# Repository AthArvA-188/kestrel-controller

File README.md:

# Kestrel

Kestrel is a design for a game controller that works with PC, Android, iPhone, and iPad. This repository holds the electronics, the enclosure, and the firmware.

Status: design files only. Nobody has built or tested a Kestrel. Every part of the design needs a prototype before it can be trusted.

## What the design covers

| Requirement | How the design answers it |
| --- | --- |
| USB-C, Bluetooth, WiFi | ESP32-S3 module with native USB, Bluetooth LE, and WiFi |
| Remote play over WiFi | The pad sends inputs straight to a receiver on the gaming PC |
| Xbox layout | Offset sticks, ABXY, D-pad, View, Menu, Home, bumpers, triggers |
| TMR sticks with a tension ring | TMR modules in the ALPS footprint. A ring under each stick preloads an added centring spring |
| Adaptive triggers | A motor, worm, and stop arm per trigger, with Hall position sensing |
| Tactile LB and RB | Micro switches |
| Four back paddles | Two per grip on micro switches, remappable |
| Backlit controls | 24 addressable RGB LEDs under translucent buttons and stick rings |
| Screen | 1.9 inch 320 x 170 display showing host, battery, and profile, with on-device remapping |
| XInput and DInput | Both over USB. Bluetooth offers an Xbox identity and a generic gamepad |
| Wider grip | 173 mm wide body with full grips |

`docs/spec.md` explains each decision.

## Layout

| Folder | Contents | Start with |
| --- | --- | --- |
| `docs/` | Specification and WiFi protocol | `docs/spec.md` |
| `shared/` | Coordinates and pin assignments that the other folders read | `layout.json`, `pinmap.json` |
| `hardware/` | KiCad schematic and PCB, generator scripts, fabrication files | `hardware/README.md` |
| `mech/` | Enclosure and mechanism CAD, STEP and STL files, renders | `mech/README.md` |
| `firmware/` | ESP-IDF firmware, native tests, screen simulator | `firmware/README.md` |
| `host/` | PC receiver for WiFi mode | `host/README.md` |

## What has been checked

| Area | Checked | Not checked |
| --- | --- | --- |
| Schematic | KiCad electrical rules check | Review by a second engineer |
| PCB | KiCad design rules check and schematic parity. Results are in `hardware/README.md` | Fabrication, assembly, power-up |
| Enclosure | Part interference, stick tilt clearance, trigger sweep, opening positions | Printing, fit, strength, feel |
| Firmware | Builds for the ESP32-S3. 49 unit tests pass on a PC. The screen UI renders in a simulator | Anything on hardware |
| WiFi receiver | 23 tests pass against a simulated pad | The virtual gamepad driver |

The screen UI below comes from the real firmware code running in the simulator.

## Biggest risks

1. **iPhone and iPad.** iOS only accepts known controllers. The firmware presents an Xbox controller's Bluetooth identity, and nobody has confirmed that this works from an ESP32. Treat Apple support as unproven.
2. **The PCB is autorouted.** It passes the rule checks, but the router ran signal tracks through the inner power layers. A layout engineer should review it before a production order. See `hardware/README.md`.
3. **The stick tension mechanism is new.** Its forces are calculated, not measured, and it may make L3 and R3 click too easily on the tightest setting.
4. **The trigger actuator is first-pass.** The gear ratio, motor, and arm geometry need tuning on a prototype.
5. **Parts need checking against their drawings.** The thumbstick module's supply pins, the micro switch footprint, the fuel gauge footprint, and the display module's pocket are listed in `docs/spec.md` under open items.

## Building a prototype

1. Read the open items in `docs/spec.md` and the "Before ordering" list in `hardware/README.md`.
2. Order the PCB from `hardware/out/fab/` and the parts in `hardware/out/kestrel-bom.csv`.
3. Print the parts in `mech/out/stl/`.
4. Build and flash the firmware as `firmware/README.md` describes.
5. Run stick, trigger, and bumper calibration from the on-screen menu.

## Third-party material

- The schematic and PCB embed symbols and footprints from the KiCad libraries, which use the CC-BY-SA 4.0 licence with an exception for designs.
- `hardware/lib/easyeda/` holds the thumbstick symbol, footprint, and 3D model converted from the EasyEDA library entry for LCSC part C146170. Check EasyEDA's terms before publishing them.
- The firmware font is generated from Aileron, a CC0 typeface.
- The Xbox-identity Bluetooth mode uses Microsoft's vendor ID and report format. That suits a personal prototype and is not cleared for a product on sale. The USB vendor ID `1209:0001` is a placeholder.

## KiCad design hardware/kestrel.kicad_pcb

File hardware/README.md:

# Kestrel main board

One four-layer PCB, 134 x 82 mm, carrying everything except the display module, battery, motors, and paddle switches. Scripts generate the schematic, the board, and the fabrication files from `gen/design.py`.

Status: generated and rule-checked. Nobody has fabricated or powered this board. Read "Before ordering" below.

## Files

| Path | Contents |
| --- | --- |
| `kestrel.kicad_pro`, `kestrel.kicad_sch`, `kestrel.kicad_pcb` | KiCad 10 project |
| `gen/` | Generator scripts. `design.py` holds the parts, nets, and placement |
| `lib/` | Project libraries: the fuel gauge symbol, the micro switch footprint, and the thumbstick part from EasyEDA |
| `out/kestrel-schematic.pdf` | Schematic |
| `out/kestrel-bom.csv` | Bill of materials, 47 lines |
| `out/fab/` | Gerbers, drill files, and the position file |
| `out/kestrel-pcb.step` | 3D model of the assembled board |
| `out/erc.json`, `out/drc.json` | Rule check reports |

## Checks

Results from the last run:

| Check | Result |
| --- | --- |
| Electrical rules check on the schematic | 0 violations. 190 symbols, 130 nets |
| Design rules check on the board | 0 errors, 102 warnings. Every warning is silkscreen text over copper, over other text, or near the edge |
| Unconnected items | 0 |
| Schematic parity (board nets and footprints against the schematic) | 0 differences |

The board has 193 footprints, 2481 track segments totalling 6.2 m, and 353 vias.

The rule set: 0.2 mm tracks and 0.15 mm clearance by default, 0.4 mm for power nets, 0.6 mm vias with 0.3 mm holes, 0.3 mm copper-to-edge. The autorouter narrows a few tracks to 0.1 mm at fine-pitch pins, so the minimum track width is 0.1 mm. These fit a standard four-layer service such as JLCPCB's. Confirm against your fabricator's limits.

## Layers

| Layer | Use |
| --- | --- |
| F.Cu | Face-side parts, signals, a VLED pour, and a VSYS pour over the power section |
| In1.Cu | Ground plane, with signal tracks through it |
| In2.Cu | VLED plane, with signal tracks through it |
| B.Cu | Battery-side parts, signals, a ground pour, and a VSYS pour |

VLED is the switched rail that feeds the LEDs and rumble motors. VSYS is the charger's system output.

The autorouter put 3.9 m of the 6.2 m of track on the two inner layers. Those tracks cut both planes into pieces. The finish stage joins the pieces again: each rail has copper on a second layer, and vias tie every island of one layer to the other. The board is fully connected, but neither inner layer is a solid plane. This is the board's main weakness. Before a production order, a layout engineer should move the signals off In1 so the ground plane is unbroken.

## Where things are

Face side: both thumbsticks, twelve tact switches, 24 LEDs with their capacitors, the LB and RB micro switches, the USB-C socket, the display connector, and the power section (charger, buck-boost, fuel gauge, load switches, 3.0 V regulator) under the display.

Battery side: the ESP32-S3 module with its antenna over the rear edge, three shift registers with pull-up arrays, the trigger motor driver, the Hall sensors, the rumble drivers, and the connectors.

| Connector | Type | Pins |
| --- | --- | --- |
| J1 | USB-C | USB 2.0 |
| J2 | JST-PH 2 | 1 battery +, 2 ground |
| J3, J4 | JST-SH 2 | Left and right trigger motors |
| J5, J6 | JST-SH 2 | Left and right rumble motors: 1 VLED, 2 switched return |
| J7, J8 | JST-SH 3 | Paddle switches: two inputs and ground |
| J9 | JST-GH 8 | Display module: VCC, GND, DIN, CLK, CS, DC, RST, BL |
| J10 | 1.27 mm header | 3V3, GND, UART TX, UART RX, EN, BOOT |

JP1 to JP4 are three-pad solder jumpers that set which outer pin of each thumbstick axis gets 3.0 V and which gets ground. They ship bridged for 3.0 V on pads 3 and 4.

SW13 is BOOT and SW14 is RESET. The bottom shell has a pinhole over each.

## Regenerating

The scripts need KiCad 10, Java 21 or later, and the Freerouting jar. Set `KICAD_ROOT` and `FREEROUTING_JAR` if they are not in the default locations at the top of `gen/build.py`. Run with KiCad's own Python:

```powershell
cd hardware\gen
$py = "$env:KICAD_ROOT\bin\python.exe"
& $py build.py sch       # schematic, ERC, PDF, netlist
& $py build.py pcb       # placed board, placement DRC, autorouter input
& $py build.py route     # autoroute (about 25 minutes), then the finish stage
& $py build.py outputs   # Gerbers, drill, position, BOM, STEP, renders
```

`build.py finish` repeats the finish stage on the saved autorouter session: it rebuilds the placed board, imports the routes, adds the pours, joins the copper islands, routes any stranded pad to its rail, and runs DRC.

The autorouter gives a different result on every run. A new run can leave a pin stranded that the finish stage cannot reach. Check that DRC reports 0 unconnected items before using the output.

`build.py route3` is an experiment that keeps In1 as a solid ground plane. It left about 40 signal connections unrouted, so the delivered board does not use it.

## Before ordering

1. **Thumbstick supply pins.** Find which outer pin of each axis is the supply on your TMR module and set JP1 to JP4 before first power-up. A reversed supply may damage the module.
2. **Thumbstick footprint.** It is the ALPS RKJXV1224005 footprint from EasyEDA. Check it against your module.
3. **Micro switch footprint.** `SW_D2FC_THT` is drawn from the usual D2FC dimensions: three pins at 5.08 mm in a 12.8 x 5.8 mm body. Check it against your switch.
4. **Fuel gauge footprint.** The MAX17048 uses KiCad's generic 2 x 2 mm DFN-8. Check the pad sizes against the datasheet.
5. **Display cable.** J9 follows the Waveshare 1.9inch LCD Module's pin order. Check the order on your module and cable.
6. **Layout review.** See "Layers". Also check the 0.4 mm power tracks against your current needs. The USB data pair is not length-matched or impedance-controlled, which full-speed USB tolerates.
7. **Parts.** Nobody has checked the BOM for stock, price, or alternates. Passive voltage ratings are given only where they matter.
8. **Charging.** The input limit is 500 mA. The TS pin has a fixed 10k resistor, so the charger does not monitor battery temperature.

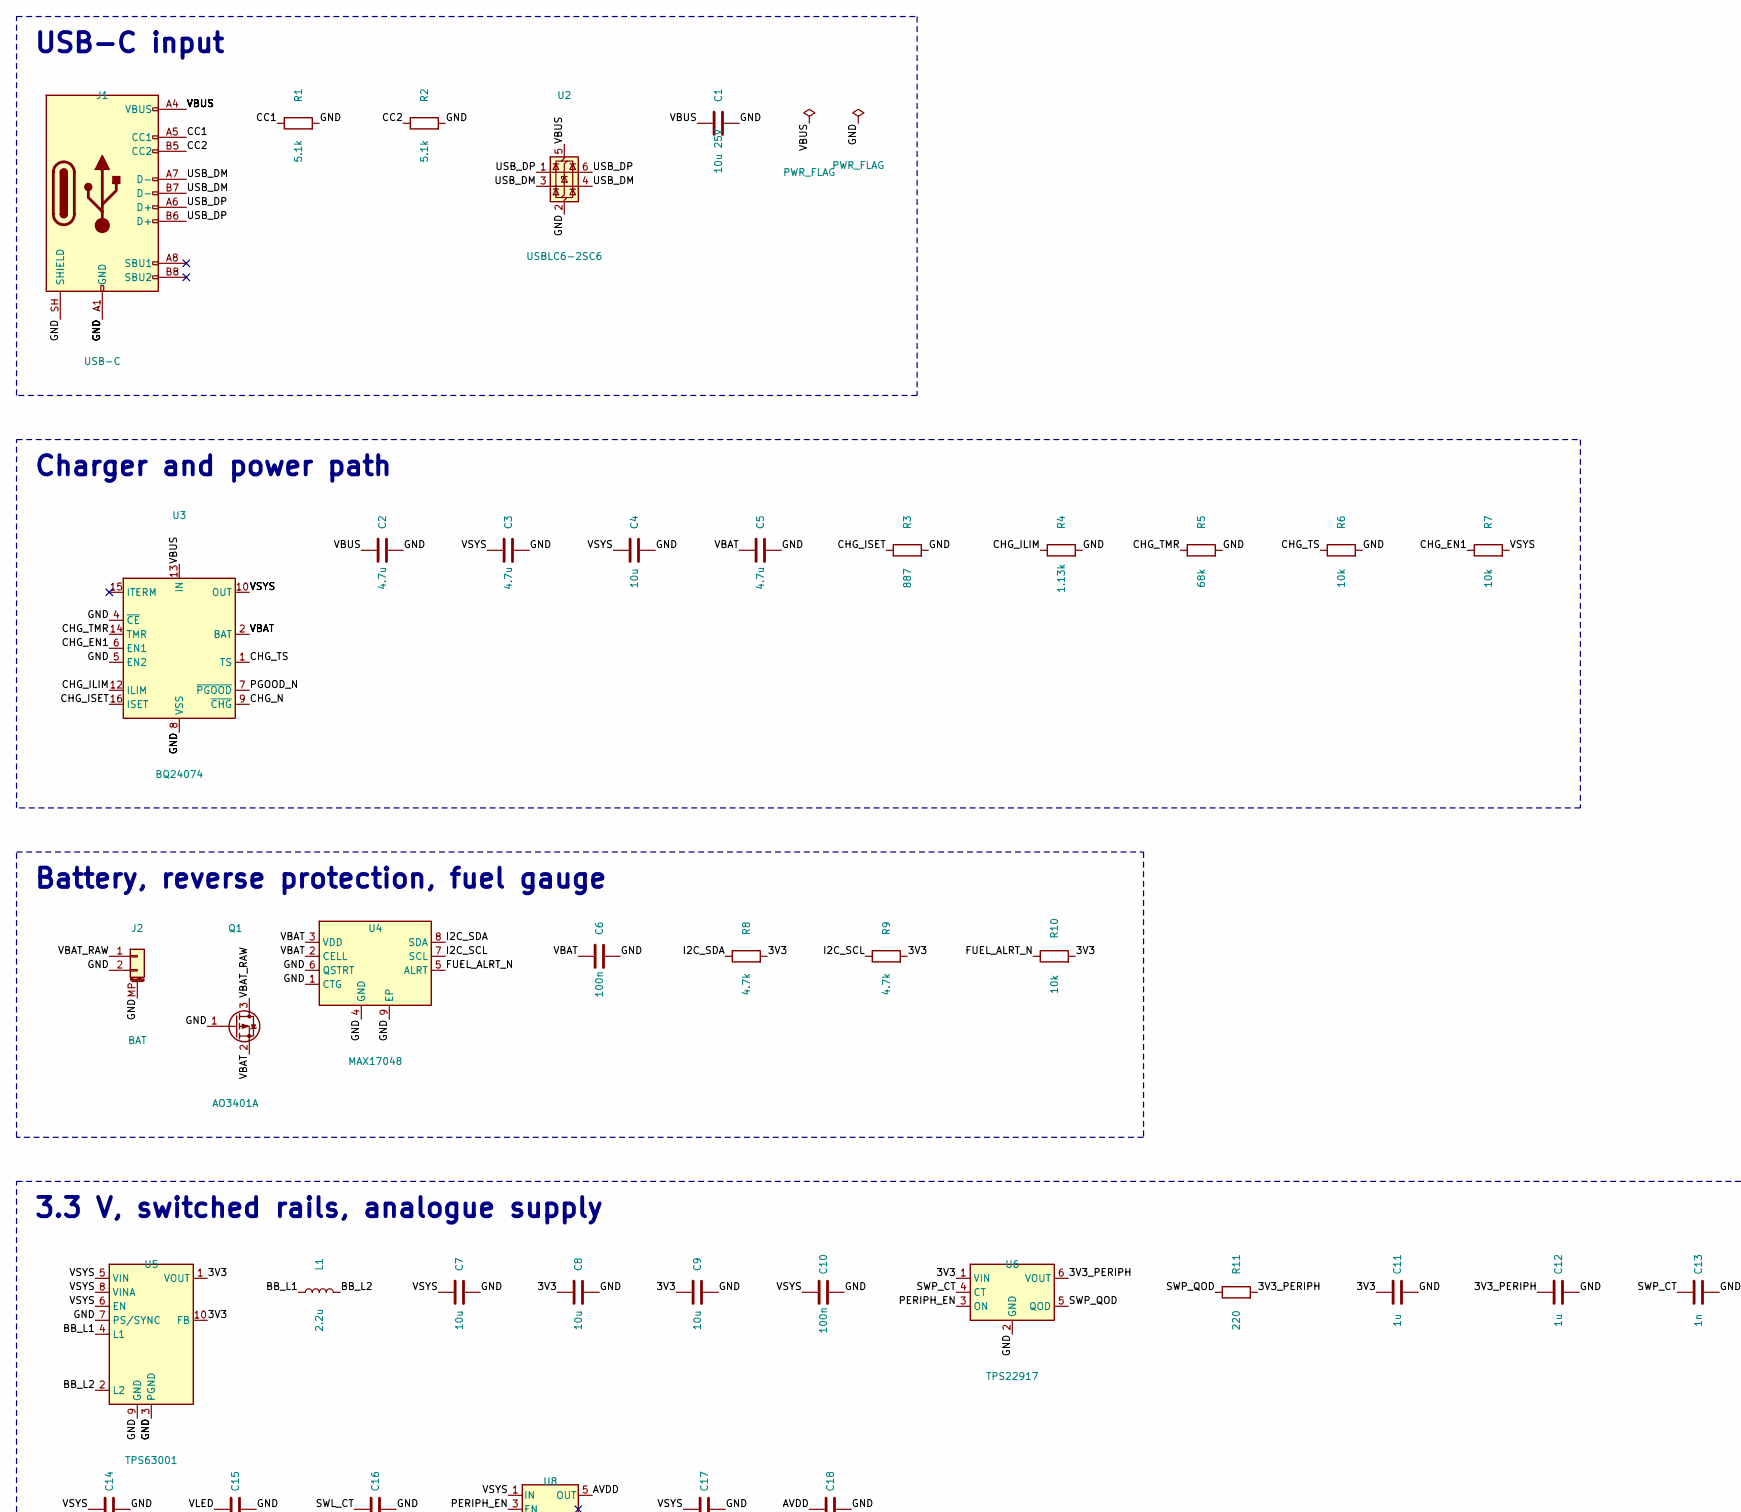
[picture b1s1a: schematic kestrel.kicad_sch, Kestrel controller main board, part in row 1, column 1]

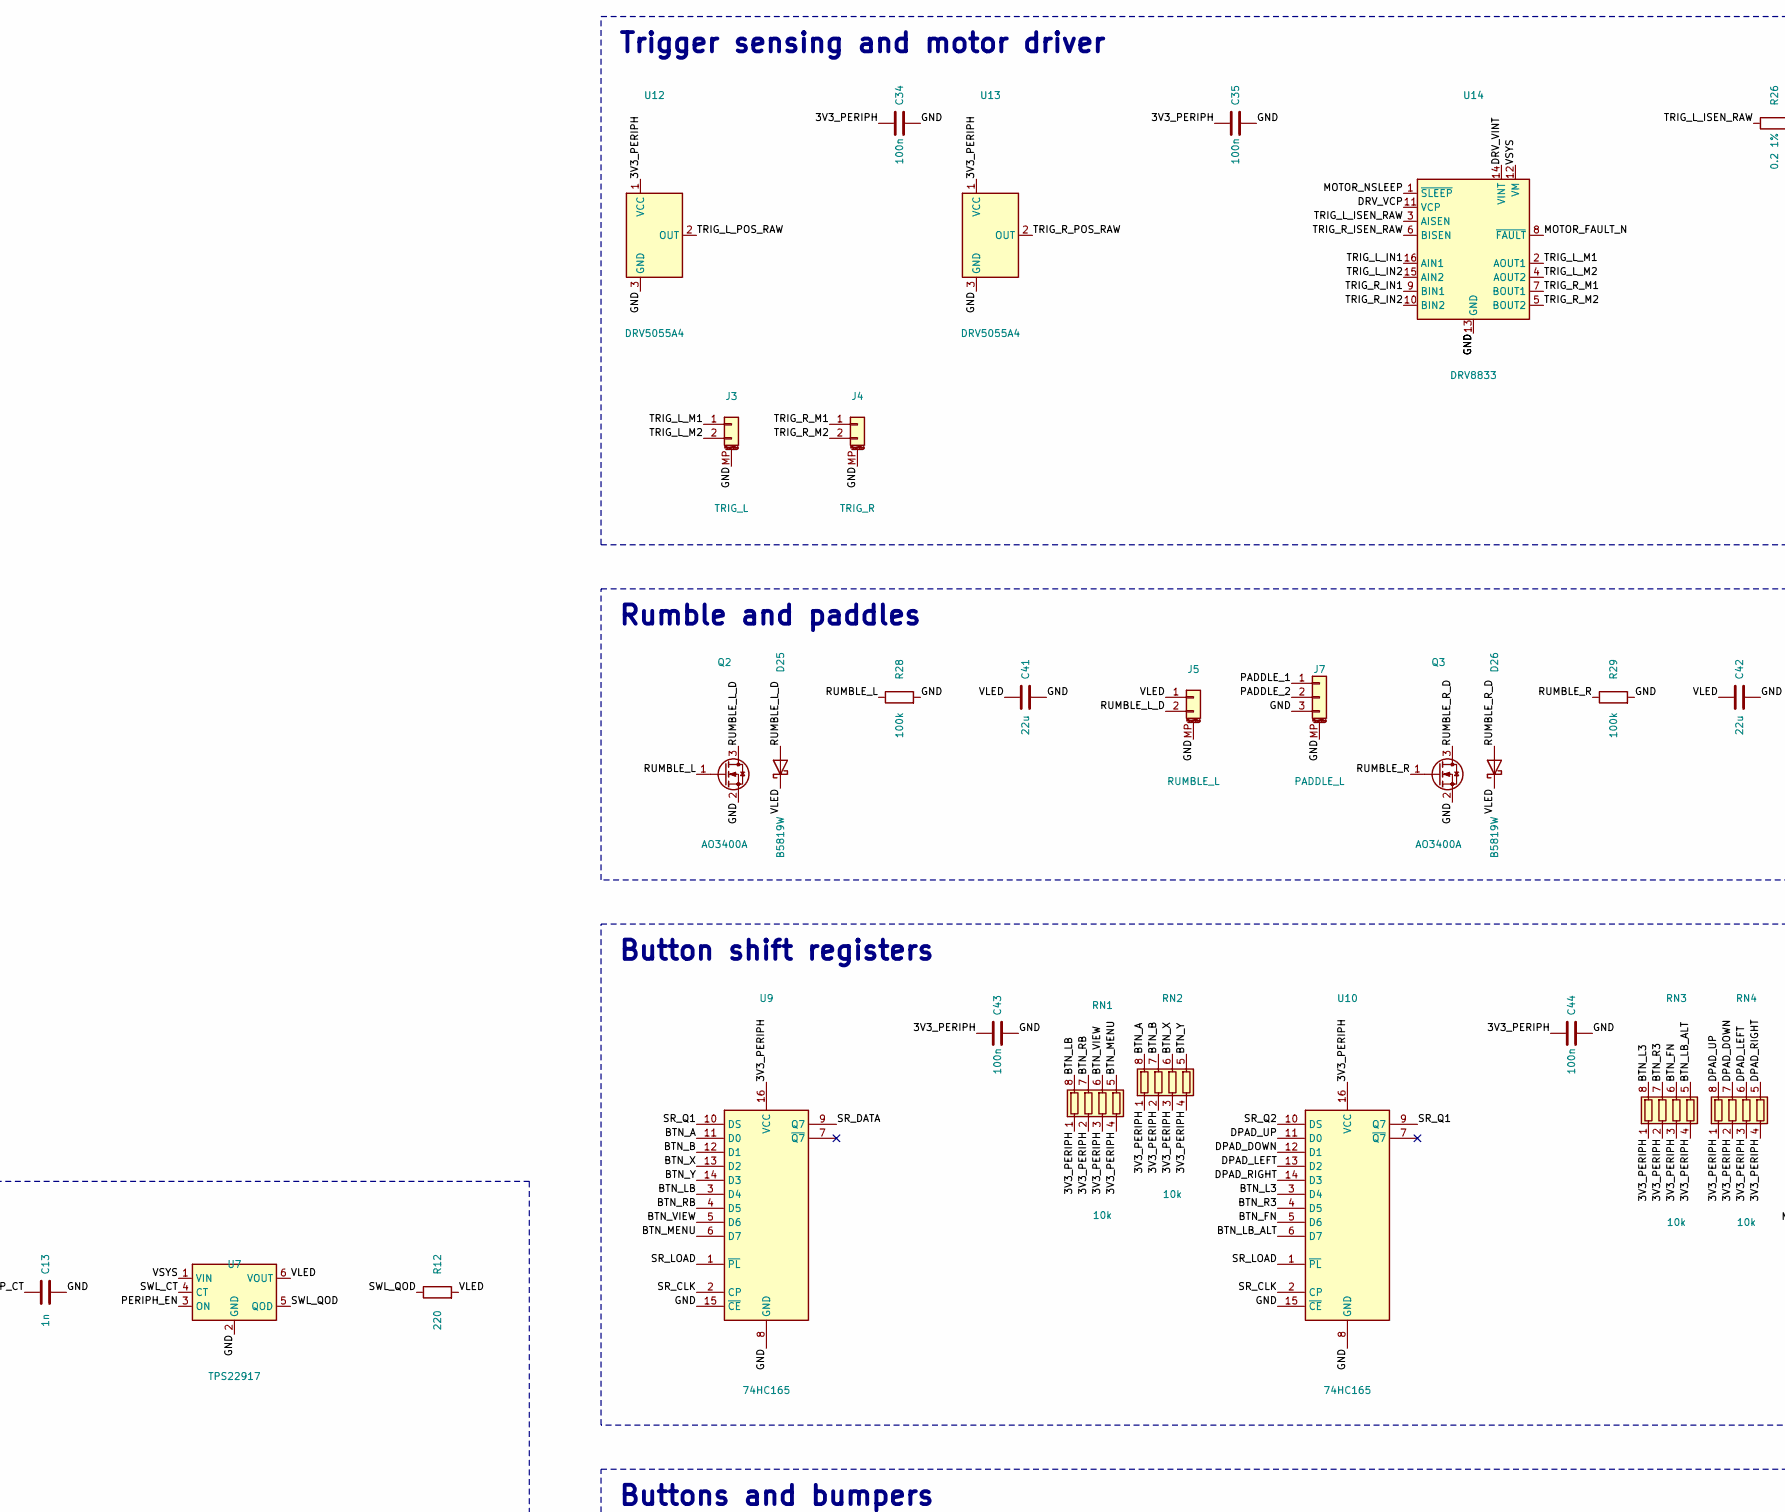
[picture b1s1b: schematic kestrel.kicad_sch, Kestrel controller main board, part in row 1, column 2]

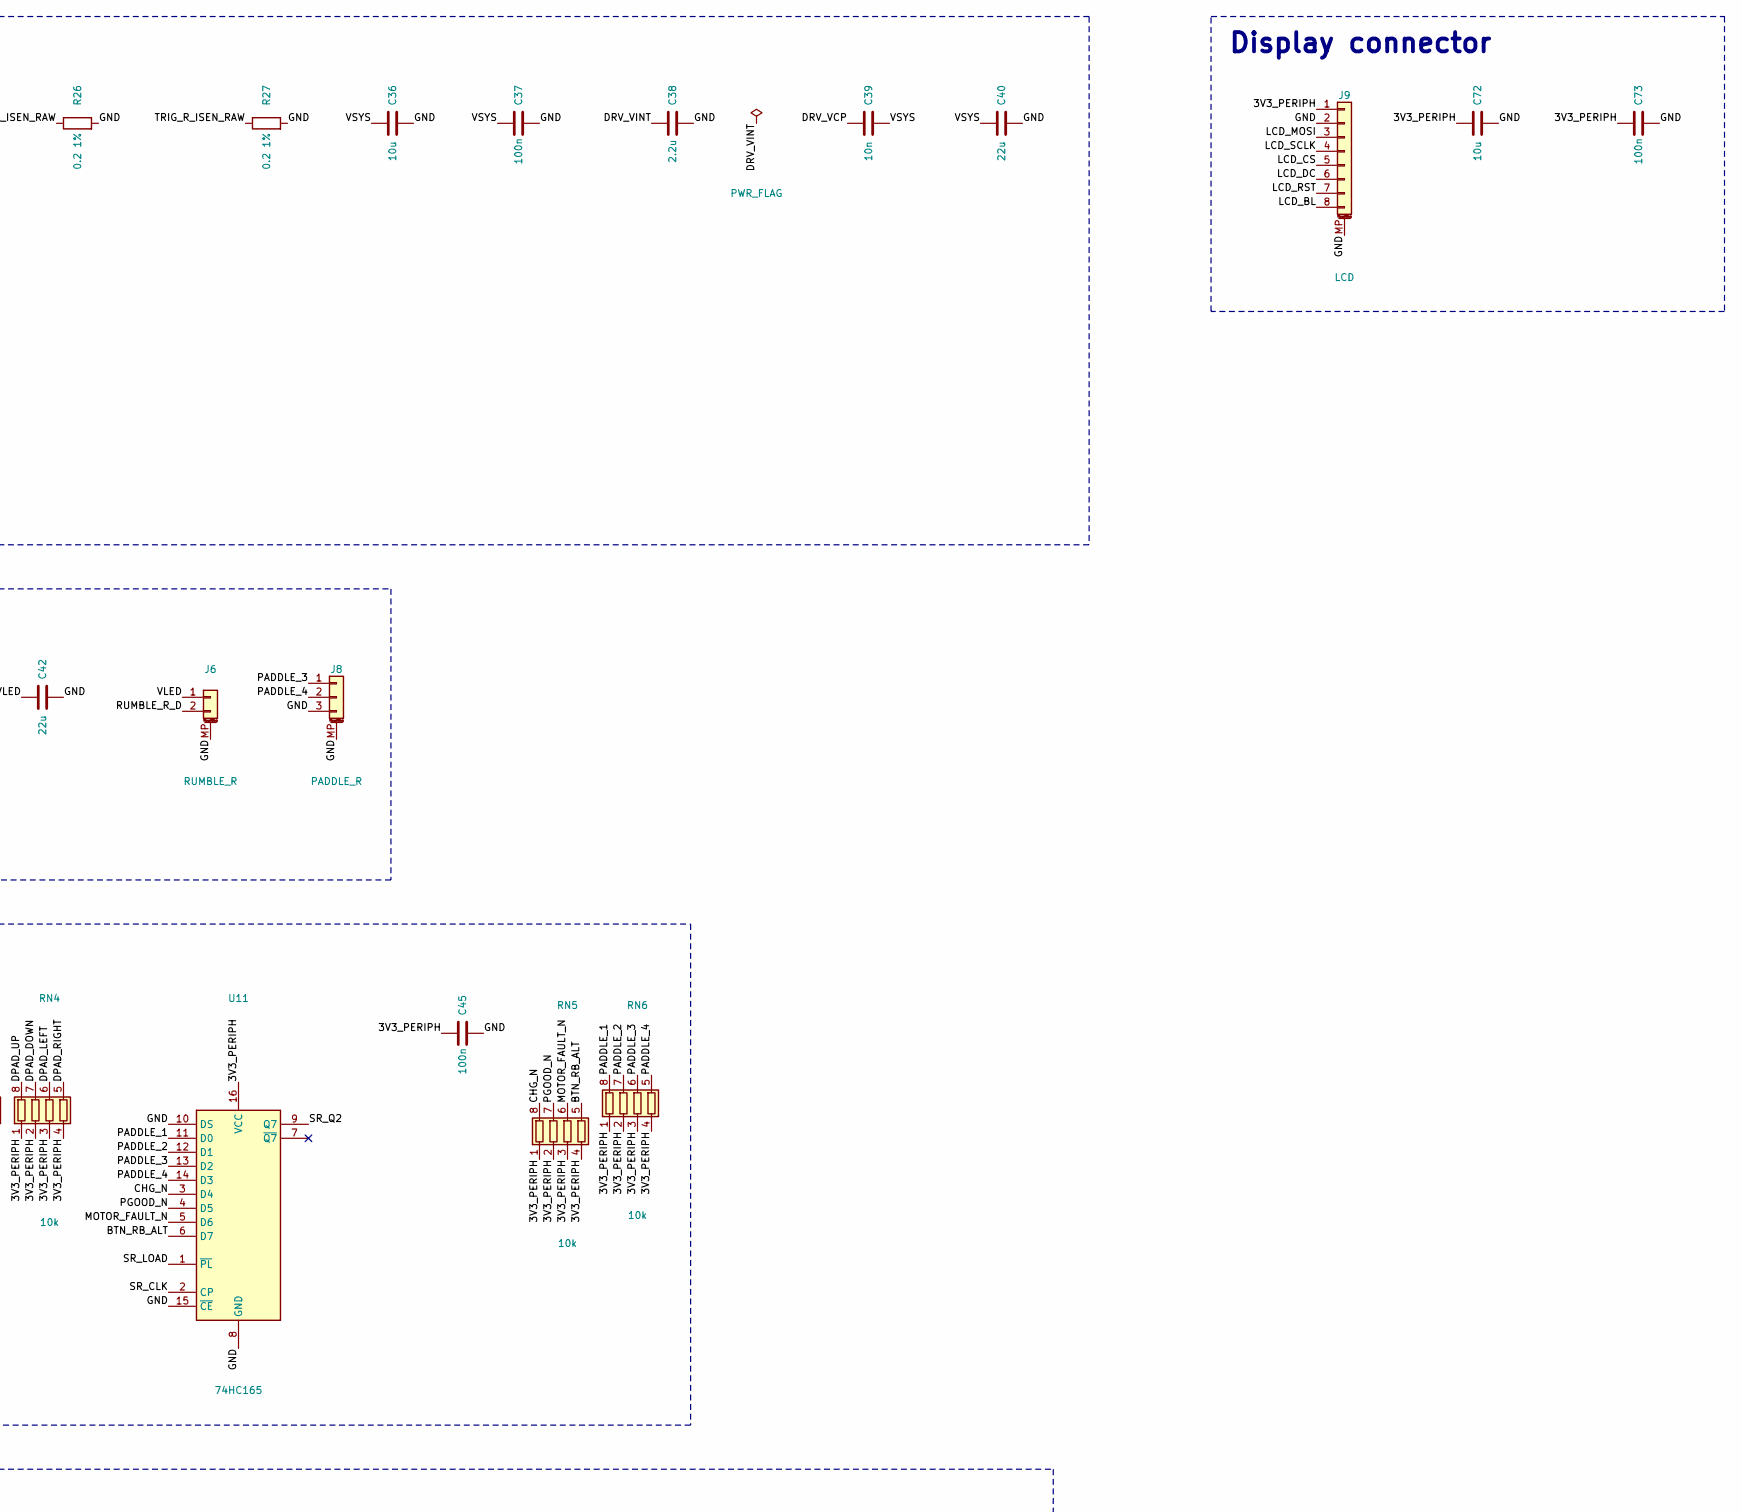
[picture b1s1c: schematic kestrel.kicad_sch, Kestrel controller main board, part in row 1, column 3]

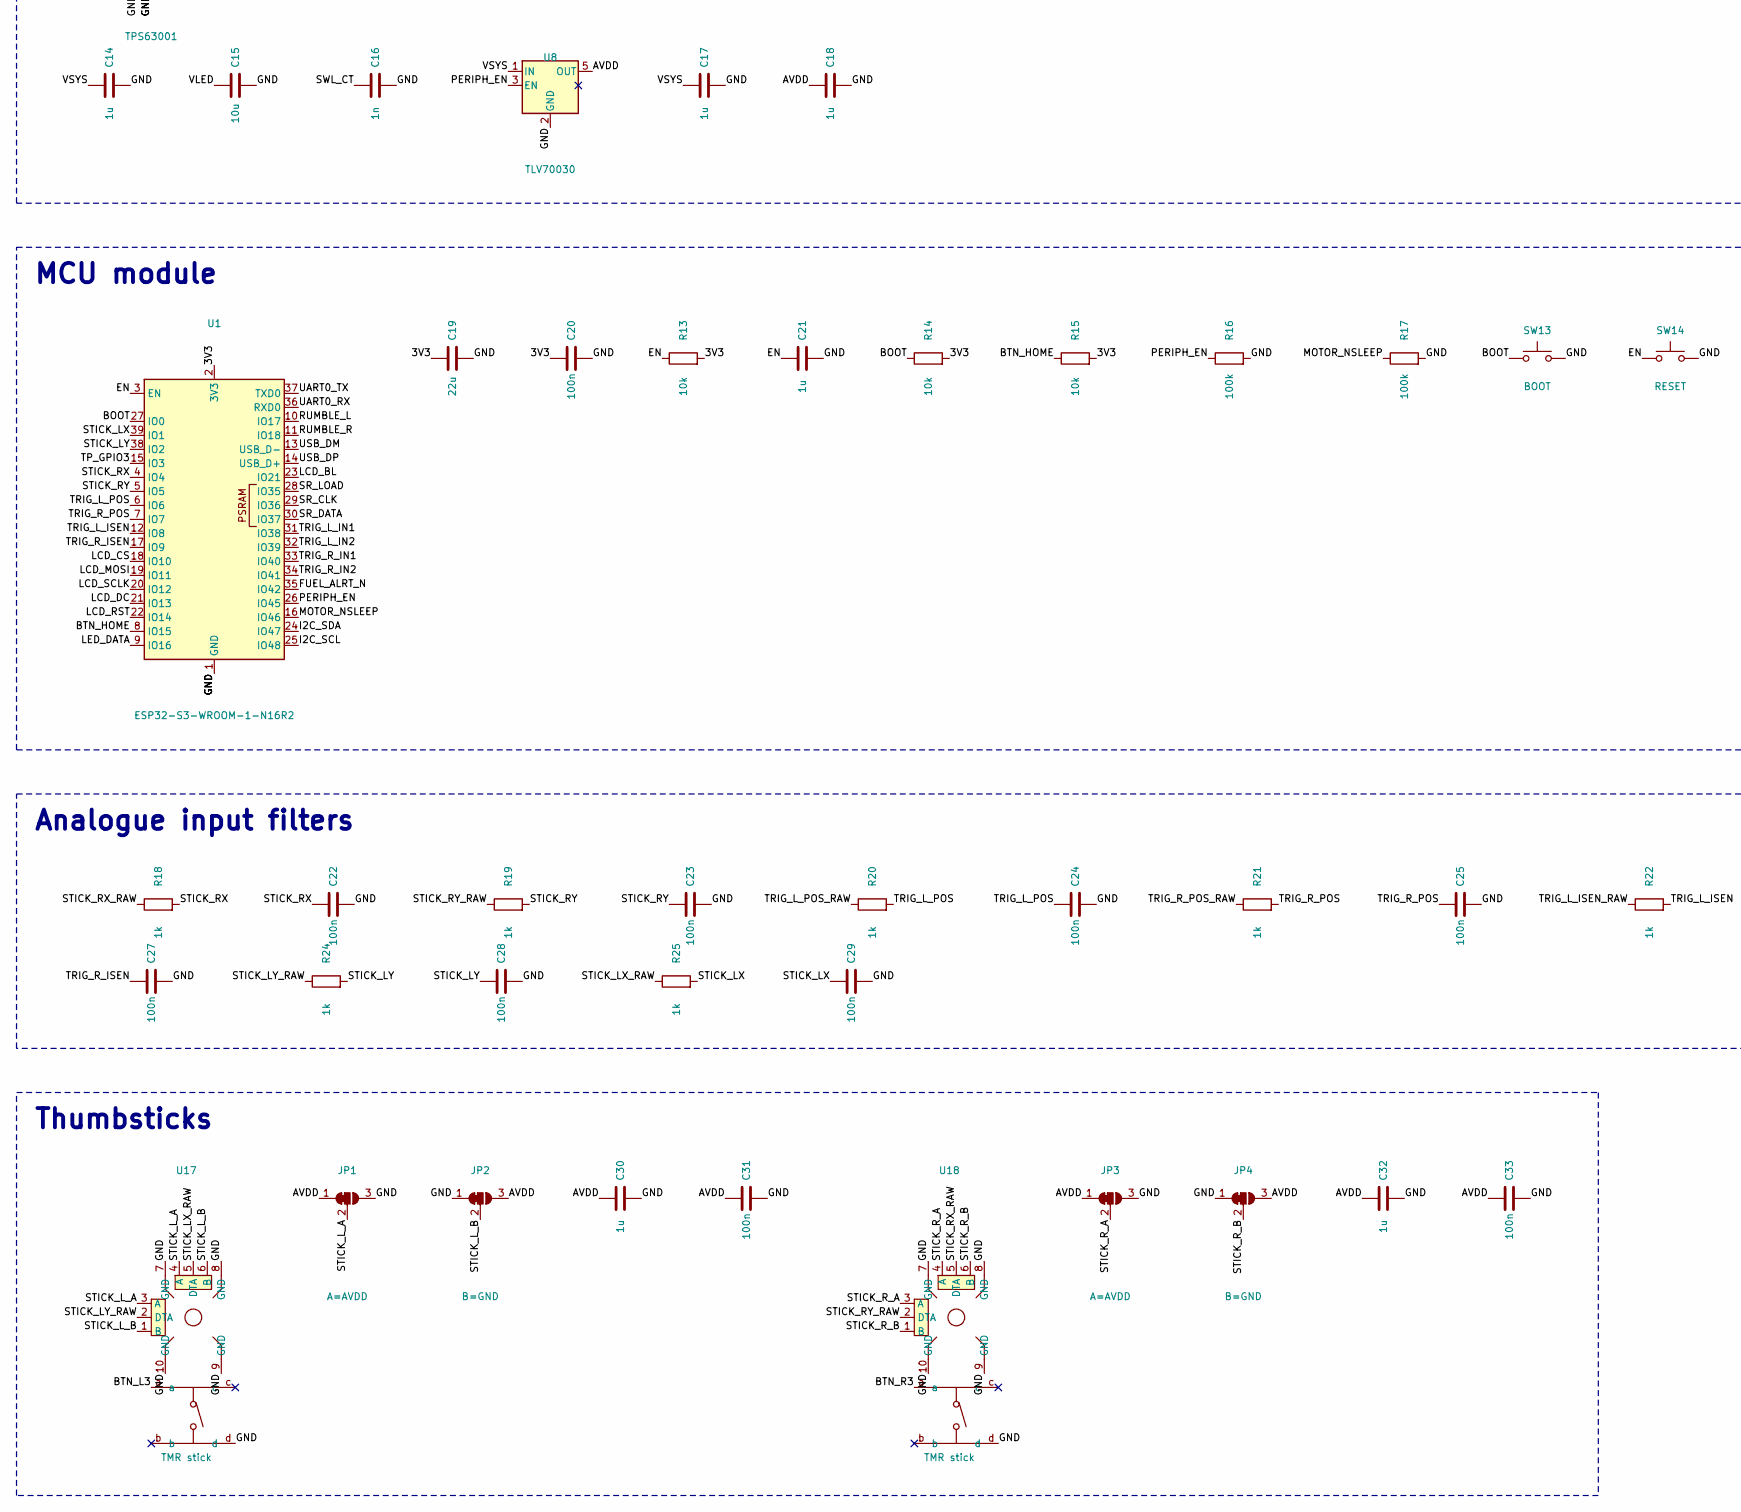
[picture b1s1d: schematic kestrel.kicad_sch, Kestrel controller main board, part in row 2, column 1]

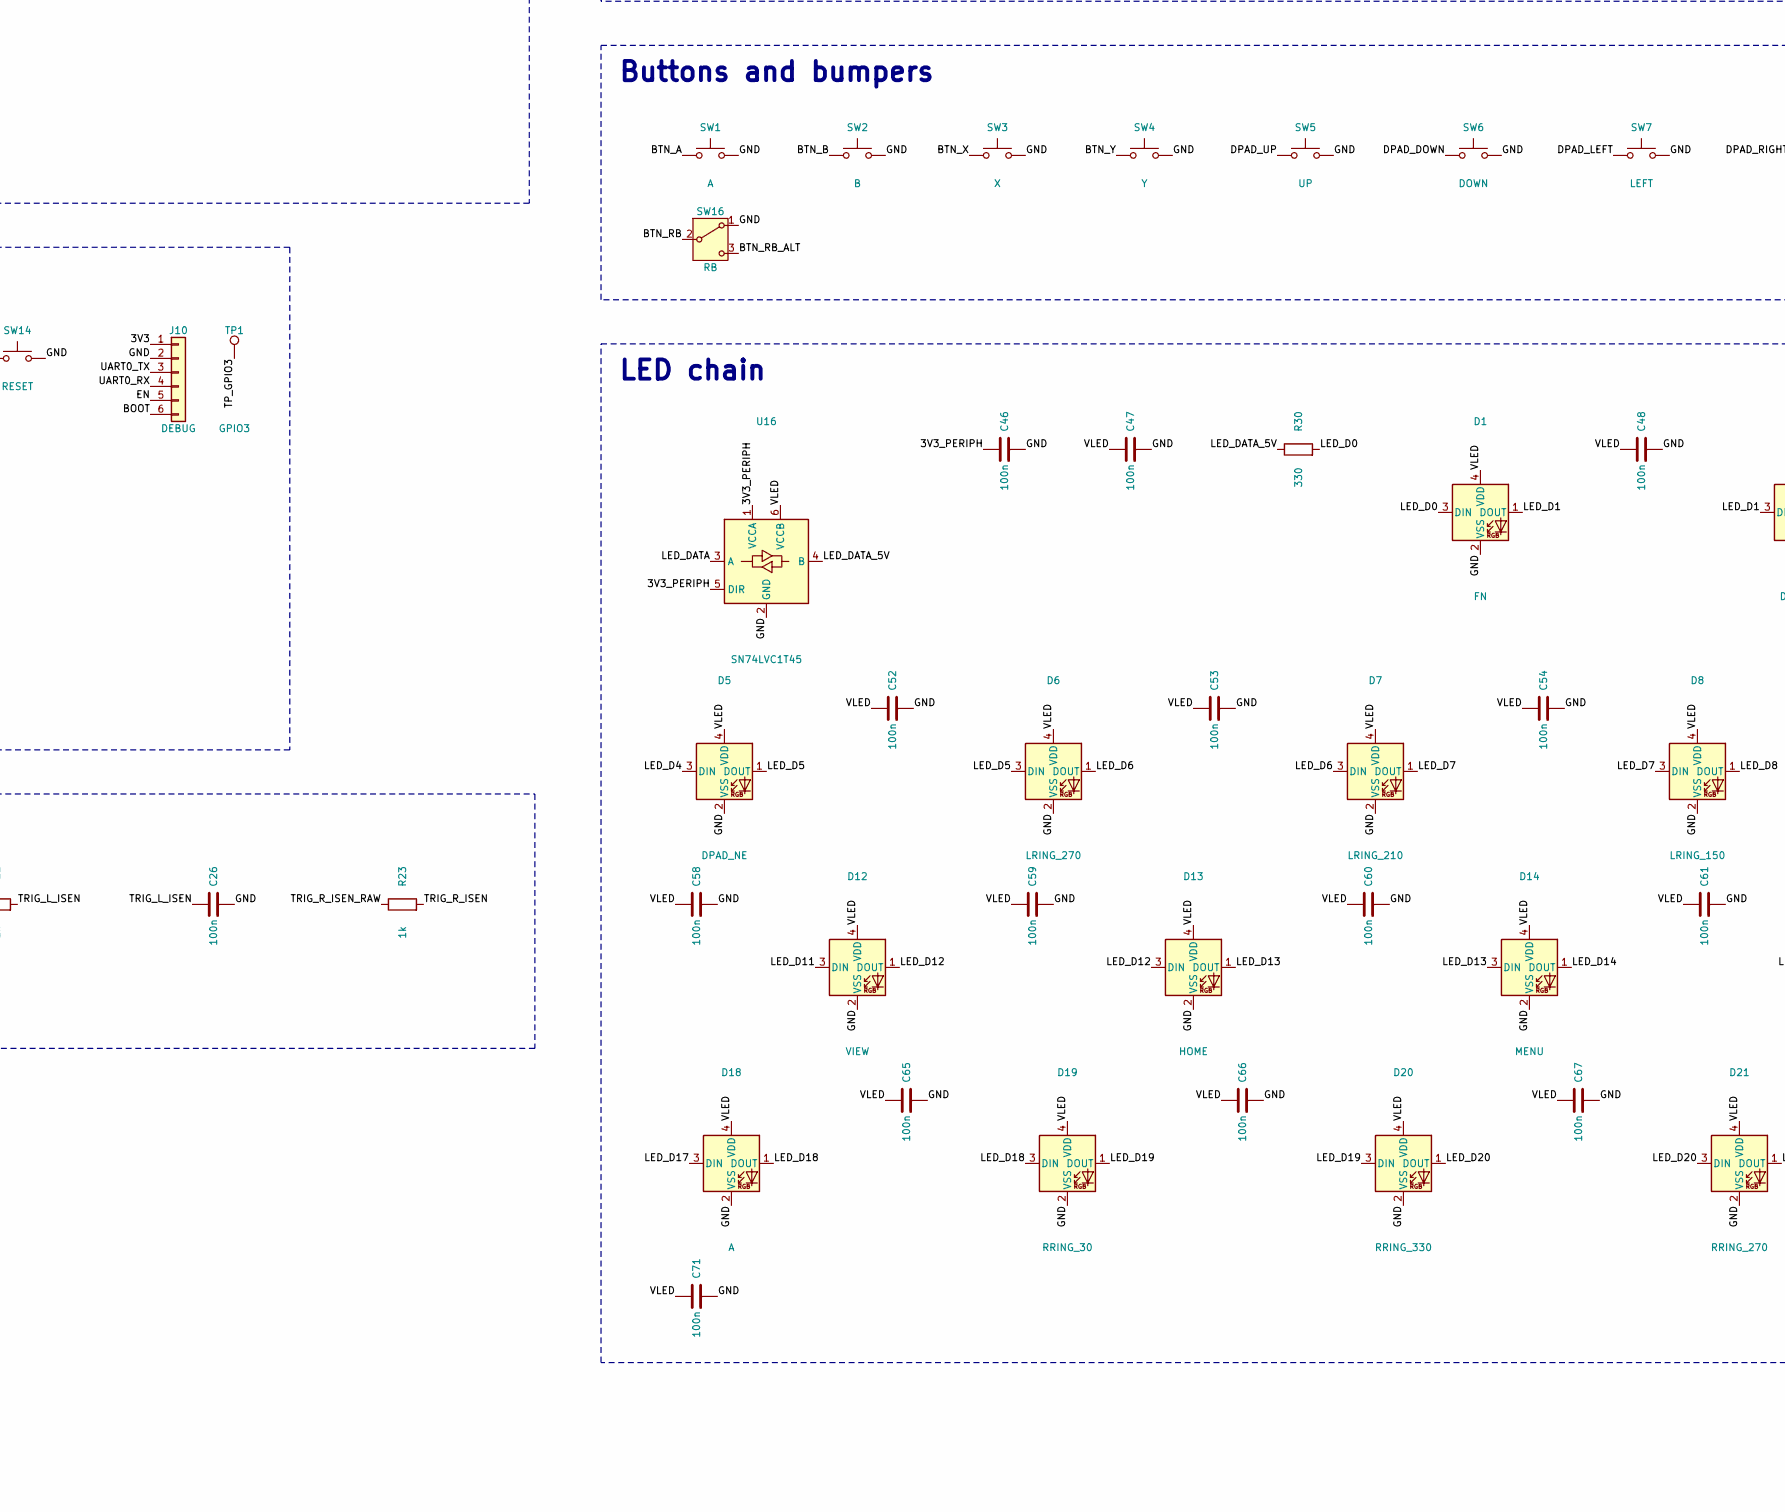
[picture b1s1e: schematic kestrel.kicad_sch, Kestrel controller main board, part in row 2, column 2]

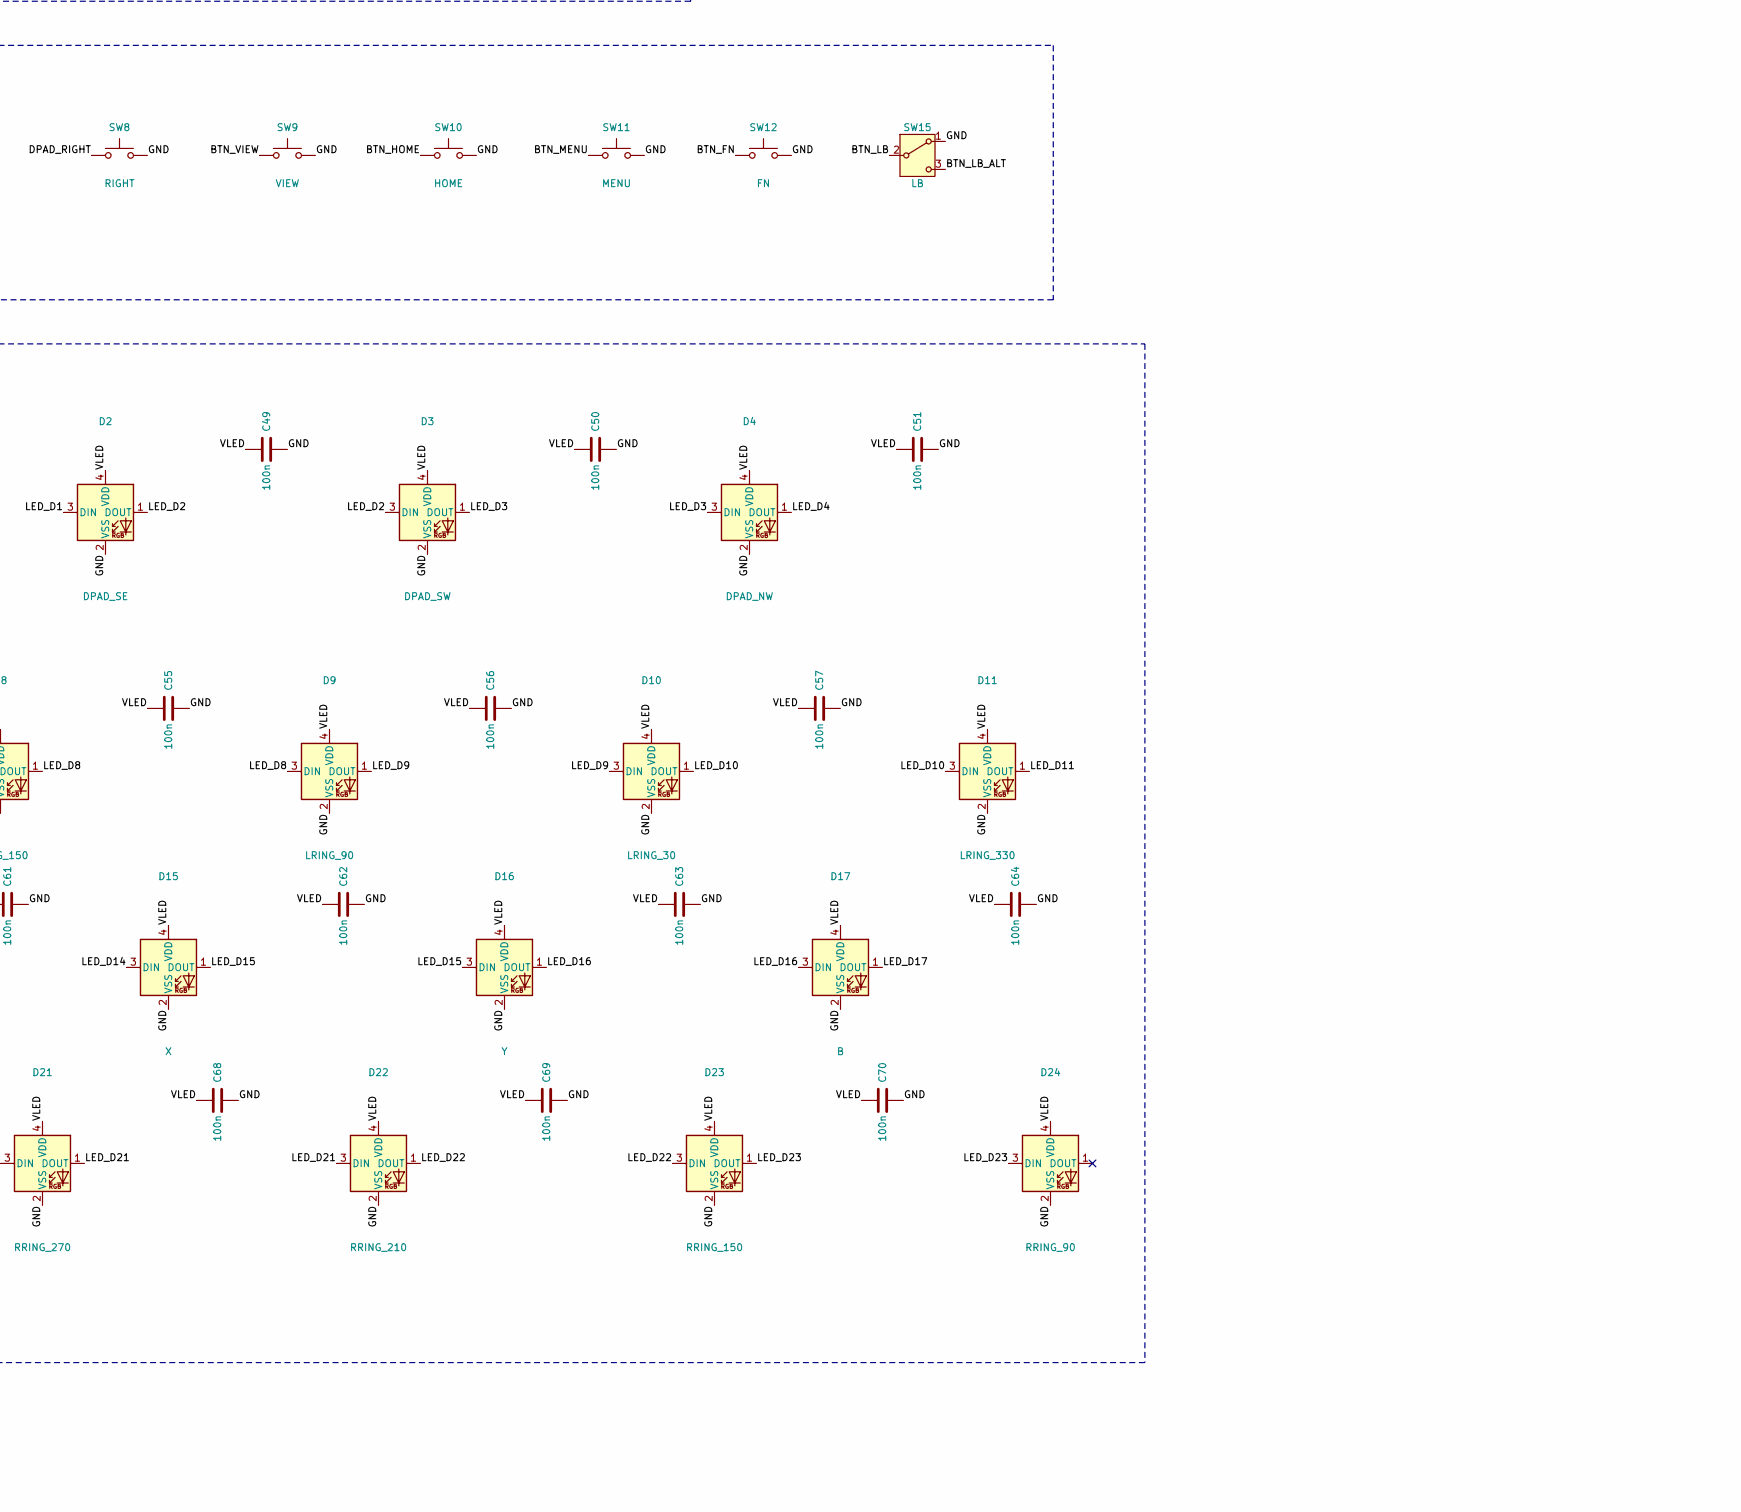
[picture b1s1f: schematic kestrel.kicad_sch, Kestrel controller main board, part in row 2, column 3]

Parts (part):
C1: 10u 25V; C_0805_2012Metric
C2, C3, C5: 4.7u; C_0603_1608Metric
C4, C7, C8, C9, C15, C36, C72: 10u; C_0805_2012Metric
C6, C10, C20, C22, C23, C24, C25, C26, C27, C28, C29, C31, C33, C34, C35, C37, C43, C44, C45, C46, C47, C48, C49, C50, C51, C52, C53, C54, C55, C56, C57, C58, C59, C60, C61, C62, C63, C64, C65, C66, C67, C68, C69, C70, C71, C73: 100n; C_0402_1005Metric
C11, C12, C14, C17, C18, C21, C30, C32: 1u; C_0402_1005Metric
C13, C16: 1n; C_0402_1005Metric
C19, C40, C41, C42: 22u; C_0805_2012Metric
C38: 2.2u; C_0603_1608Metric
C39: 10n; C_0402_1005Metric
D1: FN; LED_SK6812MINI_PLCC4_3.5x3.5mm_P1.75mm; MPN SK6812MINI
D2: DPAD_SE; LED_SK6812MINI_PLCC4_3.5x3.5mm_P1.75mm; MPN SK6812MINI
D3: DPAD_SW; LED_SK6812MINI_PLCC4_3.5x3.5mm_P1.75mm; MPN SK6812MINI
D4: DPAD_NW; LED_SK6812MINI_PLCC4_3.5x3.5mm_P1.75mm; MPN SK6812MINI
D5: DPAD_NE; LED_SK6812MINI_PLCC4_3.5x3.5mm_P1.75mm; MPN SK6812MINI
D6: LRING_270; LED_SK6812MINI_PLCC4_3.5x3.5mm_P1.75mm; MPN SK6812MINI
D7: LRING_210; LED_SK6812MINI_PLCC4_3.5x3.5mm_P1.75mm; MPN SK6812MINI
D8: LRING_150; LED_SK6812MINI_PLCC4_3.5x3.5mm_P1.75mm; MPN SK6812MINI
D9: LRING_90; LED_SK6812MINI_PLCC4_3.5x3.5mm_P1.75mm; MPN SK6812MINI
D10: LRING_30; LED_SK6812MINI_PLCC4_3.5x3.5mm_P1.75mm; MPN SK6812MINI
D11: LRING_330; LED_SK6812MINI_PLCC4_3.5x3.5mm_P1.75mm; MPN SK6812MINI
D12: VIEW; LED_SK6812MINI_PLCC4_3.5x3.5mm_P1.75mm; MPN SK6812MINI
D13: HOME; LED_SK6812MINI_PLCC4_3.5x3.5mm_P1.75mm; MPN SK6812MINI
D14: MENU; LED_SK6812MINI_PLCC4_3.5x3.5mm_P1.75mm; MPN SK6812MINI
D15: X; LED_SK6812MINI_PLCC4_3.5x3.5mm_P1.75mm; MPN SK6812MINI
D16: Y; LED_SK6812MINI_PLCC4_3.5x3.5mm_P1.75mm; MPN SK6812MINI
D17: B; LED_SK6812MINI_PLCC4_3.5x3.5mm_P1.75mm; MPN SK6812MINI
D18: A; LED_SK6812MINI_PLCC4_3.5x3.5mm_P1.75mm; MPN SK6812MINI
D19: RRING_30; LED_SK6812MINI_PLCC4_3.5x3.5mm_P1.75mm; MPN SK6812MINI
D20: RRING_330; LED_SK6812MINI_PLCC4_3.5x3.5mm_P1.75mm; MPN SK6812MINI
D21: RRING_270; LED_SK6812MINI_PLCC4_3.5x3.5mm_P1.75mm; MPN SK6812MINI
D22: RRING_210; LED_SK6812MINI_PLCC4_3.5x3.5mm_P1.75mm; MPN SK6812MINI
D23: RRING_150; LED_SK6812MINI_PLCC4_3.5x3.5mm_P1.75mm; MPN SK6812MINI
D24: RRING_90; LED_SK6812MINI_PLCC4_3.5x3.5mm_P1.75mm; MPN SK6812MINI
D25, D26: B5819W; D_SOD-123; MPN B5819W
J1: USB-C; USB_C_Receptacle_HRO_TYPE-C-31-M-12; MPN TYPE-C-31-M-12
J2: BAT; JST_PH_S2B-PH-SM4-TB_1x02-1MP_P2.00mm_Horizontal; MPN S2B-PH-SM4-TB
J3: TRIG_L; JST_SH_SM02B-SRSS-TB_1x02-1MP_P1.00mm_Horizontal; MPN SM02B-SRSS-TB
J4: TRIG_R; JST_SH_SM02B-SRSS-TB_1x02-1MP_P1.00mm_Horizontal; MPN SM02B-SRSS-TB
J5: RUMBLE_L; JST_SH_SM02B-SRSS-TB_1x02-1MP_P1.00mm_Horizontal; MPN SM02B-SRSS-TB
J6: RUMBLE_R; JST_SH_SM02B-SRSS-TB_1x02-1MP_P1.00mm_Horizontal; MPN SM02B-SRSS-TB
J7: PADDLE_L; JST_SH_SM03B-SRSS-TB_1x03-1MP_P1.00mm_Horizontal; MPN SM03B-SRSS-TB
J8: PADDLE_R; JST_SH_SM03B-SRSS-TB_1x03-1MP_P1.00mm_Horizontal; MPN SM03B-SRSS-TB
J9: LCD; JST_GH_SM08B-GHS-TB_1x08-1MP_P1.25mm_Horizontal; MPN SM08B-GHS-TB
J10: DEBUG; PinHeader_1x06_P1.27mm_Vertical
JP1, JP3: A=AVDD; SolderJumper-3_P1.3mm_Bridged12_RoundedPad1.0x1.5mm
JP2, JP4: B=GND; SolderJumper-3_P1.3mm_Bridged12_RoundedPad1.0x1.5mm
L1: 2.2u; L_Bourns-SRN4018; MPN SRN4018-2R2M
Q1: AO3401A; SOT-23; MPN AO3401A
Q2, Q3: AO3400A; SOT-23; MPN AO3400A
R1, R2: 5.1k; R_0402_1005Metric
R3: 887; R_0402_1005Metric
R4: 1.13k; R_0402_1005Metric
R5: 68k; R_0402_1005Metric
R6, R7, R10, R13, R14, R15: 10k; R_0402_1005Metric
R8, R9: 4.7k; R_0402_1005Metric
R11, R12: 220; R_0402_1005Metric
R16, R17, R28, R29: 100k; R_0402_1005Metric
R18, R19, R20, R21, R22, R23, R24, R25: 1k; R_0402_1005Metric
R26, R27: 0.2 1%; R_1206_3216Metric
R30: 330; R_0402_1005Metric
RN1, RN2, RN3, RN4, RN5, RN6: 10k; R_Array_Convex_4x0603; MPN YC164-JR-0710KL
SW1: A; SW_SPST_PTS645Sx43SMTR92; MPN PTS645SM43SMTR92
SW2: B; SW_SPST_PTS645Sx43SMTR92; MPN PTS645SM43SMTR92
SW3: X; SW_SPST_PTS645Sx43SMTR92; MPN PTS645SM43SMTR92
SW4: Y; SW_SPST_PTS645Sx43SMTR92; MPN PTS645SM43SMTR92
SW5: UP; SW_SPST_PTS645Sx43SMTR92; MPN PTS645SM43SMTR92
SW6: DOWN; SW_SPST_PTS645Sx43SMTR92; MPN PTS645SM43SMTR92
SW7: LEFT; SW_SPST_PTS645Sx43SMTR92; MPN PTS645SM43SMTR92
SW8: RIGHT; SW_SPST_PTS645Sx43SMTR92; MPN PTS645SM43SMTR92
SW9: VIEW; SW_SPST_PTS645Sx43SMTR92; MPN PTS645SM43SMTR92
SW10: HOME; SW_SPST_PTS645Sx43SMTR92; MPN PTS645SM43SMTR92
SW11: MENU; SW_SPST_PTS645Sx43SMTR92; MPN PTS645SM43SMTR92
SW12: FN; SW_SPST_PTS645Sx43SMTR92; MPN PTS645SM43SMTR92
SW13: BOOT; SW_Push_1P1T_XKB_TS-1187A; MPN TS-1187A-B-A-B
SW14: RESET; SW_Push_1P1T_XKB_TS-1187A; MPN TS-1187A-B-A-B
SW15: LB; SW_D2FC_THT; MPN D2FC-F-7N
SW16: RB; SW_D2FC_THT; MPN D2FC-F-7N
TP1: GPIO3; TestPoint_Pad_D1.0mm
U1: ESP32-S3-WROOM-1-N16R2; ESP32-S3-WROOM-1; MPN ESP32-S3-WROOM-1-N16R2
U2: USBLC6-2SC6; SOT-23-6; MPN USBLC6-2SC6
U3: BQ24074; VQFN-16-1EP_3x3mm_P0.5mm_EP1.6x1.6mm; MPN BQ24074RGTR
U4: MAX17048; DFN-8-1EP_2x2mm_P0.5mm_EP0.8x1.6mm; MPN MAX17048G+T10
U5: TPS63001; Texas_DRC0010J; MPN TPS63001DRCR
U6, U7: TPS22917; SOT-23-6; MPN TPS22917DBVR
U8: TLV70030; SOT-23-5; MPN TLV70030DDCR
U9, U10, U11: 74HC165; TSSOP-16_4.4x5mm_P0.65mm; MPN SN74HC165PWR
U12, U13: DRV5055A4; SOT-23; MPN DRV5055A4QDBZR
U14: DRV8833; HTSSOP-16-1EP_4.4x5mm_P0.65mm_EP3.4x5mm_Mask2.46x2.31mm; MPN DRV8833PWPR
U16: SN74LVC1T45; SOT-23-6; MPN SN74LVC1T45DBVR
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
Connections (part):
/3V3: C8.1, C9.1, C11.1, C19.1, C20.1, J10.1, R8.2, R9.2, R10.2, R13.2, R14.2, R15.2, U1.2 (3V3), U5.1 (VOUT), U5.10 (FB), U6.1 (VIN)
/3V3_PERIPH: C12.1, C34.1, C35.1, C43.1, C44.1, C45.1, C46.1, C72.1, C73.1, J9.1, R11.2, RN1.1 (R1.1), RN1.2 (R2.1), RN1.3 (R3.1), RN1.4 (R4.1), RN2.1 (R1.1), RN2.2 (R2.1), RN2.3 (R3.1), RN2.4 (R4.1), RN3.1 (R1.1), RN3.2 (R2.1), RN3.3 (R3.1), RN3.4 (R4.1), RN4.1 (R1.1), RN4.2 (R2.1), RN4.3 (R3.1), RN4.4 (R4.1), RN5.1 (R1.1), RN5.2 (R2.1), RN5.3 (R3.1), RN5.4 (R4.1), RN6.1 (R1.1), RN6.2 (R2.1), RN6.3 (R3.1), RN6.4 (R4.1), U6.6 (VOUT), U9.16 (VCC), U10.16 (VCC), U11.16 (VCC), U12.1 (VCC), U13.1 (VCC), U16.1 (VCCA), U16.5 (DIR)
/AVDD: C18.1, C30.1, C31.1, C32.1, C33.1, JP1.1 (A), JP2.3 (B), JP3.1 (A), JP4.3 (B), U8.5 (OUT)
/BB_L1: L1.1, U5.4 (L1)
/BB_L2: L1.2, U5.2 (L2)
/BOOT: J10.6, R14.1, SW13.1, U1.27 (IO0)
/BTN_A: RN2.8 (R1.2), SW1.1, U9.11 (D0)
/BTN_B: RN2.7 (R2.2), SW2.1, U9.12 (D1)
/BTN_FN: RN3.6 (R3.2), SW12.1, U10.5 (D6)
/BTN_HOME: R15.1, SW10.1, U1.8 (IO15)
/BTN_L3: RN3.8 (R1.2), U10.3 (D4), U17.a
/BTN_LB: RN1.8 (R1.2), SW15.2 (B), U9.3 (D4)
/BTN_LB_ALT: RN3.5 (R4.2), SW15.3 (C), U10.6 (D7)
/BTN_MENU: RN1.5 (R4.2), SW11.1, U9.6 (D7)
/BTN_R3: RN3.7 (R2.2), U10.4 (D5), U18.a
/BTN_RB: RN1.7 (R2.2), SW16.2 (B), U9.4 (D5)
/BTN_RB_ALT: RN5.5 (R4.2), SW16.3 (C), U11.6 (D7)
/BTN_VIEW: RN1.6 (R3.2), SW9.1, U9.5 (D6)
/BTN_X: RN2.6 (R3.2), SW3.1, U9.13 (D2)
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
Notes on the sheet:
Analogue input filters
USB-C input
Rumble and paddles
MCU module
Buttons and bumpers
Battery, reverse protection, fuel gauge
LED chain
Display connector
3.3 V, switched rails, analogue supply
Thumbsticks
Button shift registers
Trigger sensing and motor driver
Charger and power path
